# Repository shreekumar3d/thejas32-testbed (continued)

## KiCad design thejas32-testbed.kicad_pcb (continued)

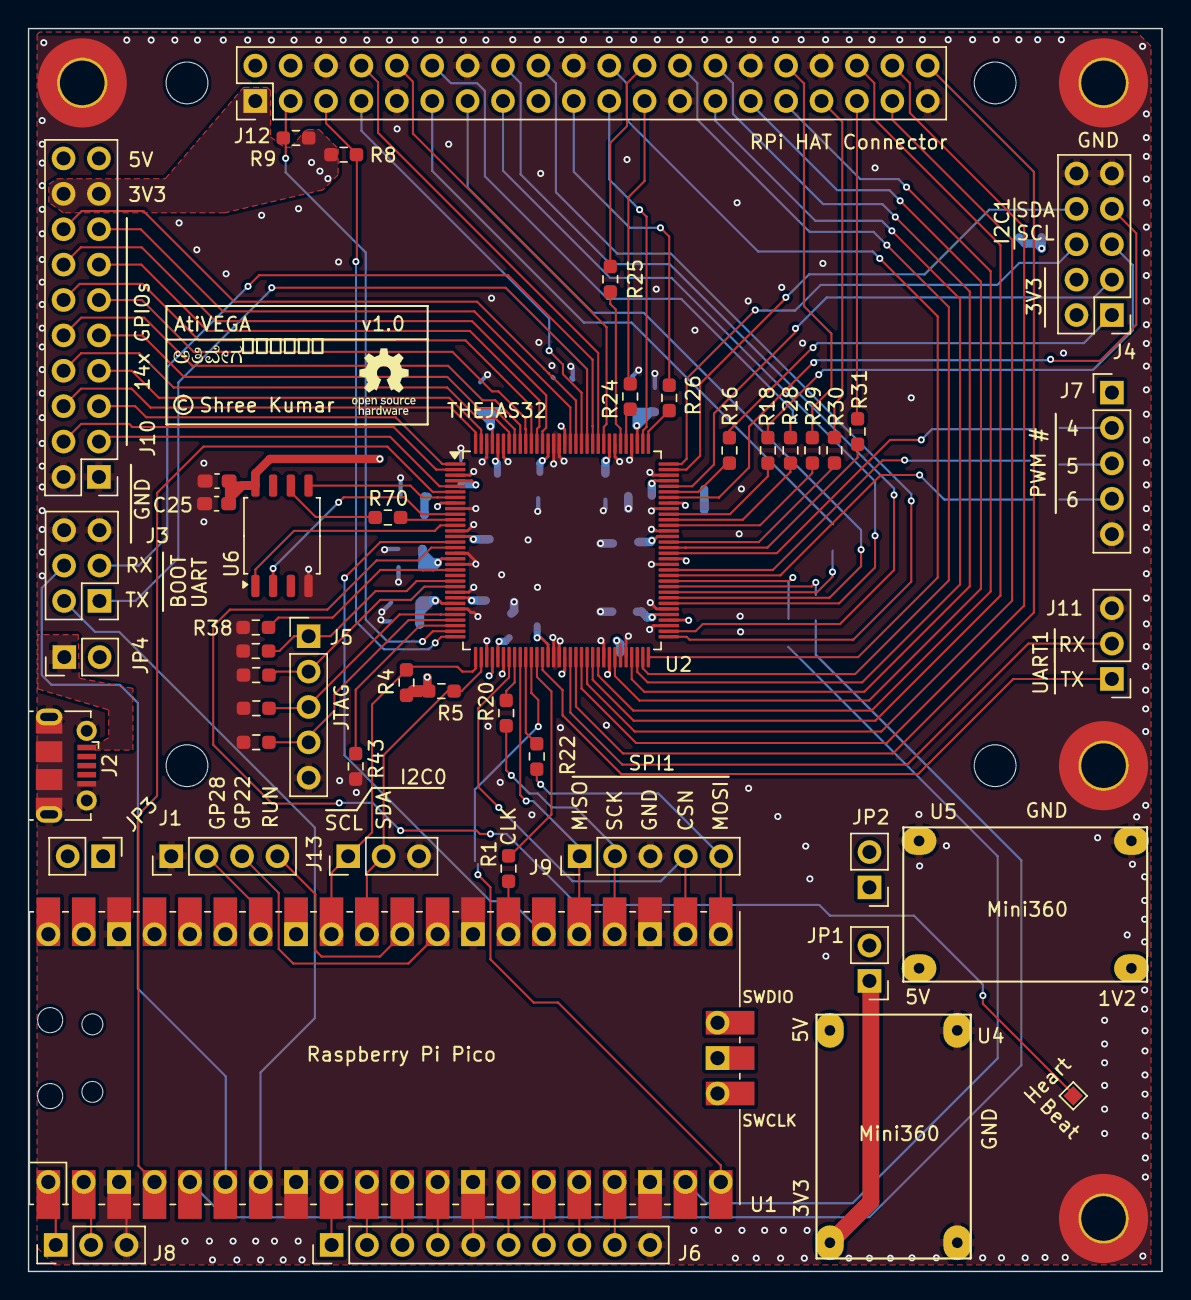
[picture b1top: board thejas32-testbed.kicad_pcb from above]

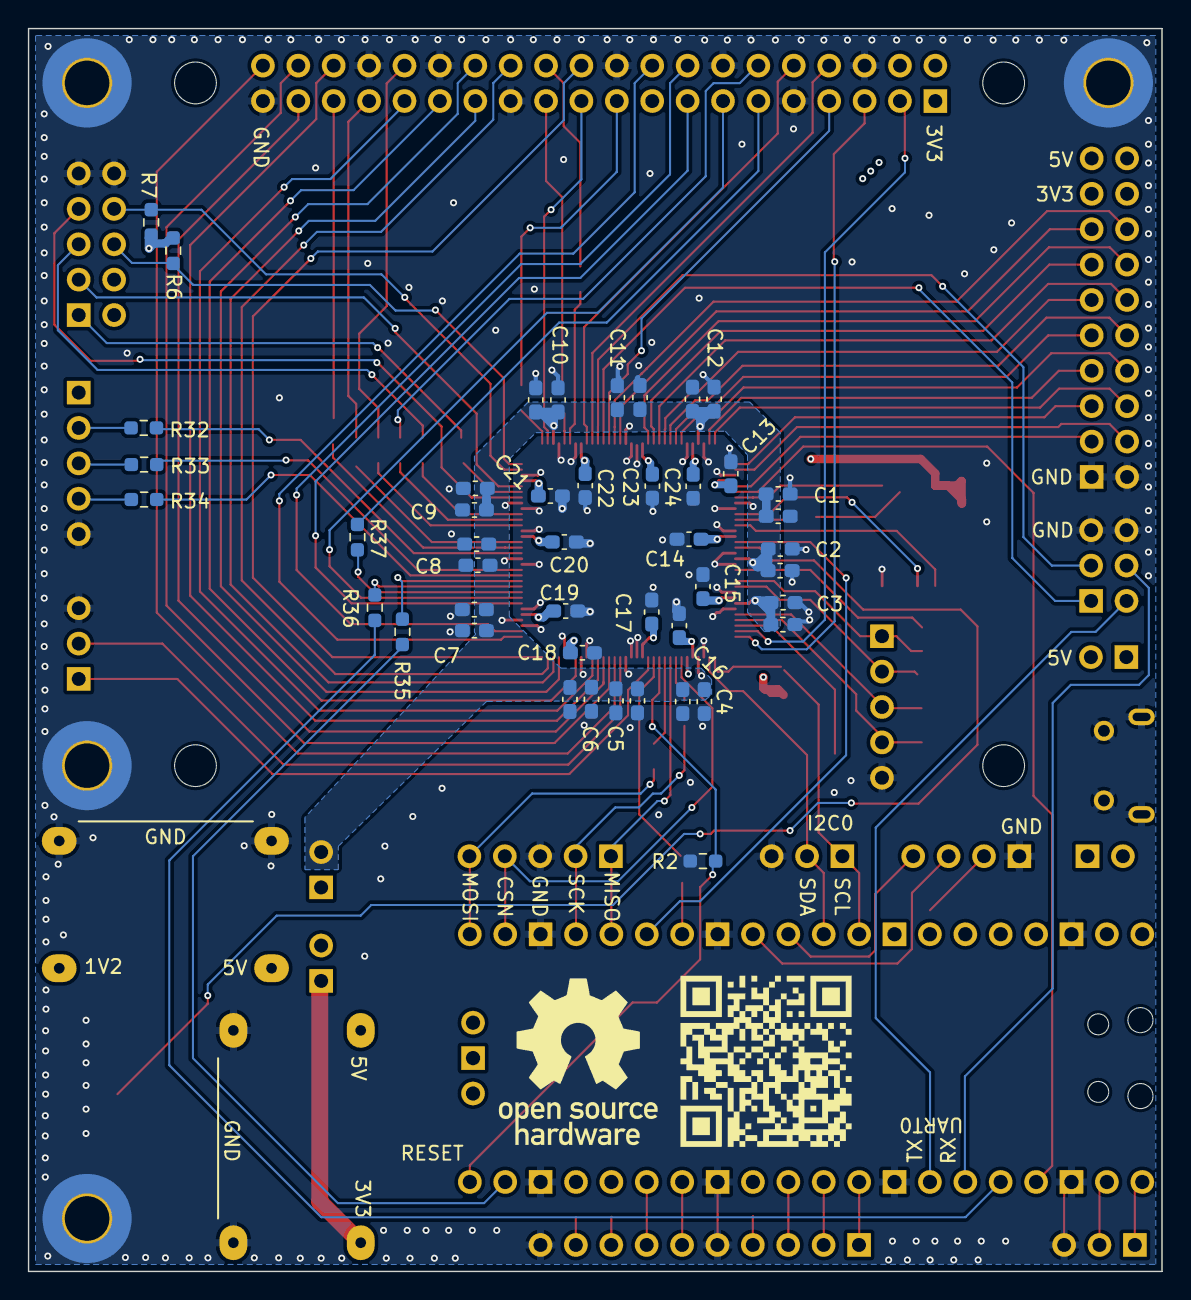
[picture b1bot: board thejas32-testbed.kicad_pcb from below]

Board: 4 copper layers, 81.4 x 89.2 mm, 101 parts (45 on the bottom side), 120 nets.

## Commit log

2024-03-08 Base design, prep for review
2024-03-08 Project intro, status.
2024-03-08 Add git checkout instructions.
2024-03-08 Add PTH on board edges
2024-03-08 Board stackup from Atharava's board
2024-03-09 Add footprint for Mini360
    Roughly tested using calipers against a physical module.
    Source of footprint:
    https://github.com/rayvburn/KiCad/tree/master/Mini360_step_down_converter/Mini360_step-down.pretty
    Commit 69583e8
2024-03-16 Various simplifications, initial routing.
    This is a commit for review.
    Schematic is modified to remove many zero ohms. RPi
    connector brought in.
    Layout shows 3V3 and 1V2 power planes. Pin mapping
    may need to change to avoid usage of layer 3 for
    signals if possible.
2024-03-20 Review,power shapes,dcap placement from Atharva
    All dcaps are now at layer 4, leaving lot
    more space on layer 1 for signal breakout.
    Flow of 1V2 power is deemed good - power plane,
    flowing to caps, through via to pins. Flow of 3V3
    power is reasonable - power plane with vias to both
    caps and pins.
2024-03-21 Remap pins for less criss cross. Get rid of tracks
    Got rid of tracks to start tracks afresh once placement is
    done.
2024-03-21 Reduce criss cross further with mapping changes
2024-03-21 Point KiCad-RP-Pico to fork.
2024-03-22 Potentially cleaner routing
    Main changes:
    - No more than 1 via on high speed trace (e.g. SPI)
    - Use two vias on slower GPIOs to maintain topology
    - Use via on the thick 5V trace supplying power to
    RPi connector
2024-03-22 Cleanup project files
    Removed Mini360_Buck_Module - it's in Project-Specific
    Removed empty project_lib
2024-03-22 Nicely routed PCB, clean lines
    Reasonable spacing between traces. Could be improved.
    Done for testing mostly.
2024-03-22 Minor schematic changes
    Mounting holes are M3 pads.
    PWM pin routed to Pico is excluded from header
    Position of connectors improved.
2024-04-04 Single pico, new layout
    Figured two picos was too much as a concept. So, simplify.
    Reduce number of jumpers etc also (especially in passthrough).
    The single pico breaks out pins conveniently for users for
    usage.
2024-06-17 Incorporated most review comments.
    Used 5 mils traces in breakout area. This results in very few DRC
    errors iff track spacing is set to 5 mils. However, setting it to
    8 mils (in board settings) does complain essentially for every pad
    of the THEJAS32. Those just need to be waived off.
    Ensure 16 mils track separation, except in breakout area. This can
    be verified by setting the track spacing to 16 mils and running the
2024-06-17 Heartbeat moved near mini360s
    Also corrected the file path of the 3D model for the
    flash IC
2024-06-18 Cleanup and beautification for review.
    Added silkscreen for all components.
    Grouped schematic for reading clarity.
    No circuit level changes, few nets renamed.
2024-06-18 Ready for review, all comments included
    All MPNs are provided
    Silkscreen updated
    BOM generation corrected.
2024-07-10 Update status to reflect development
2024-07-24 Updates from review
    Some major changes:
    1. JTAG connector
    2. Cleaned up layout in breakout area
    3. Improved MCU_CLOCK routing
    4. Alignment on right side jumpers
    5. 5V included in J10
2024-07-24 Align Pico USB connector to board edge
    Also moved J8, J6 and J9 to the left to match the Pico.
2024-07-24 Doc update
2024-07-24 Doc updates
2024-08-06 USB footprint changed to Molex-105017-0001
    This component is very close to Sunrom Part 4653
    https://www.sunrom.com/p/microusb-connector-with-through-hole-support-legs
    I am using the footprint from Molex, but the board
    will use the Sunrom part.
2024-08-06 Fix component properties
    Added manufacturer, corrected MPN and description
    These aren't provided for berg connectors
2024-08-06 Fix silkscreen for GPIO pin
2024-08-06 3d model of MicroUSB connector
2024-08-06 Nice PCB top view from KiCAD render
2024-08-08 Address review comments from Atharva
    Various changes:
    1. Deleted GND via near R9
    2. Added vias near corner mounting holes
    3. Thermal spoke width 40 mils for PWR_5V
    on 3rd layer
    4. Fix square trace near J10.19
2024-08-08 Update board render with silkscreen
2024-08-11 PCB and Silkscreen improvements
    Added a couple of vias to create grounds between
    traces. Moved a couple of traces to improve ground
    near Pico.
    Added github link as QR code on bottom silk
2024-08-11 Aligned with JLCPCB
    0 DRC errors, 4 warnings.
    Impedance matching on board - selected layer stackup on JLCPCB
    is JLC04161H-3313. So, 6 mil traces have 50 ohm impedance.
    Changed all 8 mil traces to 6 mils now. There are no "breakout"
    traces - as everything is normalized to 6 mils. Existing 5 and
    5.5 mil traces also promoted to 6 mils.
2024-08-11 Include CONTRIBUTORS file
2024-08-11 Update CREDITS
2024-08-12 Cleanup
    Cleaned up a few 8 mils signal tracks
    Used Tools | Cleanup Tracks & Vias... This cleans
    up tracks in pads, merges linear tracks, etc.
    Aligned JTAG resistors in a line.
2024-08-12 PCB top view image on black background
2024-08-12 Fixed 7 mils GND and PWR traces near THEJAS32
2024-08-12 Trace clearance set exactly to avoid 122 DRCs on THEJAS32
    Any higher than 0.15 mm will cause 122 DRCs exactly on
    THEJAS32 pads. 0.15 mm shows up as 5.90551 mils.
    With this setting DRC errors are 0. Looks like the right
    thing to do to me.
2024-08-12 Review fixes
    Move silkscreen away from CLK trace
    Fix jigglies in traces near THEJAS32
2024-08-13 v1.0 10 boards at JLCPCB
2024-08-13 Add PCB views in README for better github ux
2024-09-01 Bringup!
    poweron sample brings up THEJAS32 and dumps the UART log.
2024-09-01 Moved hw related files to new directory
2024-09-01 Moved missed files to hw directory
2024-09-01 Usage notes
2024-09-01 Blink LED on UART receive
    This serves as an activity indicator, but more importantly,
    serves as indirect "proof" of THEJAS32 system clock.
2024-09-01 Cosmetic and formatting changes
2024-09-01 Documentation for poweron sample
2024-09-02 Detailed board description
2024-09-02 Poweron with automatic baud rate detection.
    It's not bug free, but it "works". Everything isn't thought
    through well for all cases. YMMV.
2024-09-02 3D model of Pico reflects WH, with 2xsingle row socket mount.
    This better reflects how the Pico is being mounted now on the
    board. We mount 2 single row 20 pin sockets. Onto this, Pico
    with headers soldered is pushed.
2024-09-02 Rough Mini360 3D model
    The trimpot is much larger in this model. Couldn't find the right
    one. Mini360 looks much fancier in this 3D model.
2024-09-03 Better Mini360 model
    Got the trimpot model from
    https://grabcad.com/library/evm3e-1
    Fixed the inductor using a fileted cuboid, matching the
    mesurements of the inductor on the mini360. Material
    doesn't match, but that level of accuracy isn't required.
    Also, the MP2307 is a smaller SO package. Fixed that and
2024-09-05 Fixed autobaud detection
    Tested all the way from 150 MHz to 62.5 kHz of T32 clock
2024-09-06 Working uart boot. Hacky, but works
    Based on older autobaud detection, which won't work in all cases.
    Not clean, commiting for archival. Tomorrow is IndiaFOSS - first
    demo so I don't have time to mess around.
    This needs cleanup, but will do for now.
2024-09-06 Sample hello world
2024-09-06 New directory to hold samples and binaries
2024-09-06 Fix bad commit
2024-09-06 Working SSD1306 I2C module sample
2024-09-06 Timer Interrupt Test
    Toggles LED, dumps toggle count on UART
2024-09-12 IndiaFOSS 2024 talk slides
    Title : Open Source In and For Indian Chips
2024-09-12 Update status
2024-10-12 Remove unavailable USB connector model
2024-10-15 Use VRML model for 3D rendering
    My 3D printed jig generator can't handle STEP files yet.
    Now using the step file converted to VRML with FreeCAD.
    No change in functionality.
2024-10-18 Soldering helper jig created with pcb-asm-jig-gen
    I checked the 2x20 header for a nice fit.
    Then generated the jig for the entire board. Saving
    the scad file also as the tool is under heavy
    development.
    Observations of the 3D print:
    PCB fits flush inside the lip. Good thing is that
2024-10-29 Fix height of female headers used with Pico
    The 1x20 female headers available here locally are taller than the
    the 3d model in the design. The plastic shroud is 8.4 mm tall, as
    opposed to 7 mm in PinHeader_1x20_P2.54mm_Vertical
    To correct this, I have moved the headers and the pico upward up
    1.4 mm.
    An alternative was the change the model, but I found this simpler
2024-10-29 Tolerance tuned for no flex on 2x20 berg in jig
